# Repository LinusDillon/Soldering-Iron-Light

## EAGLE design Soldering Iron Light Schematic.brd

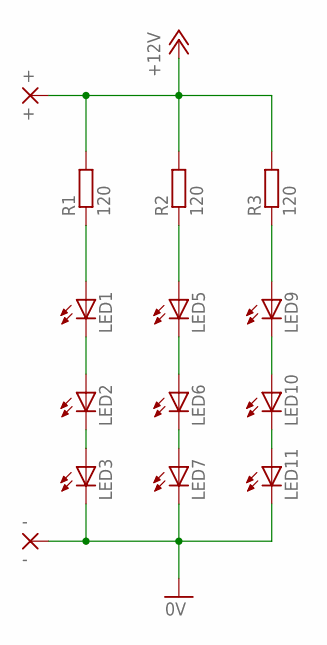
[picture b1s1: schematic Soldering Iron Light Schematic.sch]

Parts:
+: +; SMD1,27-2,54
-: -; SMD1,27-2,54
LED1, LED2, LED3, LED5, LED6, LED7, LED9, LED10, LED11: LEDCHIPLED_1206; CHIPLED_1206
R1, R2, R3: 120; R0805

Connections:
+12V: +.1, R1.2, R2.2, R3.2
GND: -.1, LED3.C, LED7.C, LED11.C
unnamed: LED1.A, R1.1
unnamed: LED5.C, LED6.A
unnamed: LED5.A, R2.1
unnamed: LED1.C, LED2.A
unnamed: LED9.A, R3.1
unnamed: LED9.C, LED10.A
unnamed: LED10.C, LED11.A
unnamed: LED6.C, LED7.A
unnamed: LED2.C, LED3.A

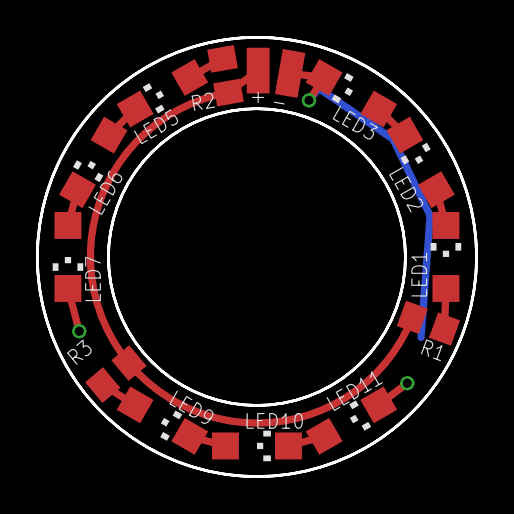
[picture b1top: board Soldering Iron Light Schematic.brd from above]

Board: 2 copper layers, 24.4 x 24.4 mm, 14 parts (0 on the bottom side), 11 nets.

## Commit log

2015-04-25 Initial check-in
